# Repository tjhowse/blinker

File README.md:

# Blinker

This is a project to create a long-lifespan solar powered device that blinks
a morse code message. All of the CAD, code and PCB design is open source, and
created with open source tools.

CAD: https://www.freecadweb.org/

PCB: https://www.kicad.org/

Code: Python and C.

Build journal/docs: https://wiki.tjhowse.com/doku.php?id=projects:blinker:overview

## V2

I2C EEPROM

https://www.st.com/en/memories/m24128-bf.html

## Component rev history

Swapped out the schottky diode for a version in JLC's basic parts list.

### Old:

https://jlcpcb.com/partdetail/23350-B5817WSSJ/C22623

20V 450mV@1A 1A SOD-323 Schottky Barrier Diodes (SBD) ROHS

### New:

https://jlcpcb.com/partdetail/GuangdongHottech-1N5819WS/C191023

40V 600mV@1A 1A SOD-323 Schottky Barrier Diodes (SBD) ROHS

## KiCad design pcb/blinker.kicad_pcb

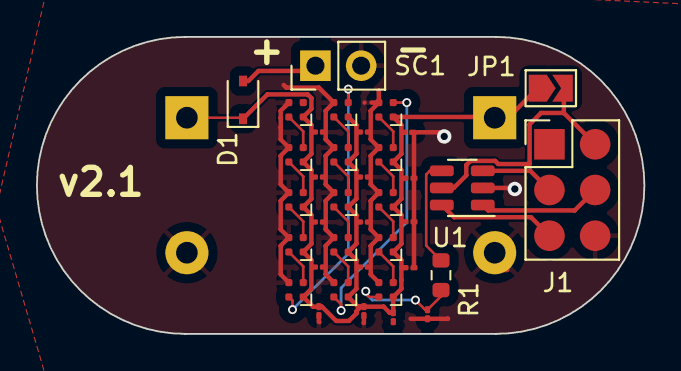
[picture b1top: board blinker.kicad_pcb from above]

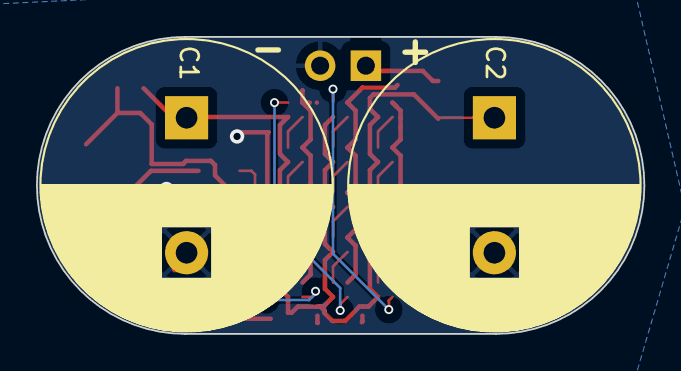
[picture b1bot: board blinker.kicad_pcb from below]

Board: 2 copper layers, 33.8 x 16.5 mm, 39 parts (2 on the bottom side), 23 nets.

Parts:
C1, C2: C_Polarized; CP_Radial_D16.0mm_P7.50mm
C3, C4, C5, C6, C7, C8, C9, C10, C11, C12, C13, C14, C15, C16, C17: 0.1uF; C_01005_0402Metric
C18: 120pF; C_01005_0402Metric
D1: D_Schottky; D_SOD-323
D2, D3, D4, D5, D6, D7, D8, D9, D10, D11, D12, D13, D14, D15, D16: LED; LED_LTST-E133CEGBK
J1: ISP; AVRISP_6PAD
JP1: Jumper_2_Open; SolderJumper-2_P1.3mm_Open_TrianglePad1.0x1.5mm
R1: 33Ω; R_0603_1608Metric
SC1: 3; PinHeader_1x02_P2.54mm_Vertical
U1: ATtiny10-TS; SOT-23-6

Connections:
2.7VCC: C1.1, C2.1, C3.2, C4.2, C5.1, C6.2, C7.2, C8.2, C9.2, C10.2, C11.2, C12.2, C13.2, C14.2, C15.2, C16.2, C17.2, D1.1 (K), D2.1 (VDD), D3.1 (VDD), D4.1 (VDD), D5.1 (VDD), D6.1 (VDD), D7.1 (VDD), D8.1 (VDD), D9.1 (VDD), D10.1 (VDD), D11.1 (VDD), D12.1 (VDD), D13.1 (VDD), D14.1 (VDD), D15.1 (VDD), D16.1 (VDD), JP1.1 (A)
5VCC: J1.2, JP1.2 (B), U1.5 (VCC)
/SLR_IN: D1.2 (A), SC1.1 (+)
GND: C1.2, C2.2, C3.1, C4.1, C5.2, C6.1, C7.1, C8.1, C9.1, C10.1, C11.1, C12.1, C13.1, C14.1, C15.1, C16.1, C17.1, C18.1, D2.3 (VSS), D3.3 (VSS), D4.3 (VSS), D5.3 (VSS), D6.3 (VSS), D7.3 (VSS), D8.3 (VSS), D9.3 (VSS), D10.3 (VSS), D11.3 (VSS), D12.3 (VSS), D13.3 (VSS), D14.3 (VSS), D15.3 (VSS), D16.3 (VSS), J1.6, SC1.2 (-), U1.2 (GND)
LEDSTRING: R1.1, U1.4 (PB2)
unnamed: C18.2, D2.2 (DIN), R1.2
unnamed: D2.4 (DOUT), D3.2 (DIN)
unnamed: D3.4 (DOUT), D4.2 (DIN)
unnamed: D4.4 (DOUT), D5.2 (DIN)
unnamed: D5.4 (DOUT), D6.2 (DIN)
unnamed: D6.4 (DOUT), D7.2 (DIN)
unnamed: D7.4 (DOUT), D8.2 (DIN)
unnamed: D8.4 (DOUT), D9.2 (DIN)
unnamed: D10.4 (DOUT), D11.2 (DIN)
unnamed: D9.4 (DOUT), D10.2 (DIN)
unnamed: D11.4 (DOUT), D12.2 (DIN)
unnamed: D12.4 (DOUT), D13.2 (DIN)
unnamed: D13.4 (DOUT), D14.2 (DIN)
unnamed: D14.4 (DOUT), D15.2 (DIN)
unnamed: D15.4 (DOUT), D16.2 (DIN)
RESET: J1.5, U1.6 (~RESET/PB3)
ROMSCL: J1.3, U1.3 (PB1)
ROMSDA: J1.4, U1.1 (PB0)

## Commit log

2022-01-26 More.
2022-01-26 About to route PCB.
2022-01-26 Ignore kicad backups.
2022-01-26 Remove backups.
2022-01-26 Routed
2022-01-26 routed.
2022-01-26 Update readme, muck about with importing the circuit model to freecad.
2022-01-26 Final PCB design?
2022-01-26 Fix zener selection.
2022-01-26 Gotta fix the rotation on U1.
2022-01-27 v1.0 PCB
2022-01-27 Fix readme.
2022-01-28 Add fab drawing.
2022-02-17 Fix rotation of D2. The JLC team picked this up and fixed it on v1.0.
2022-02-25 Discharge testing logs
2022-02-26 Hack hack.
2022-02-27 Add basic readme.
2022-02-27 Change vector name. Try interrupt-only mode.
2022-02-27 Finally working. Cleanup time.
2022-02-27 Working better.
2022-02-27 Readme update
2022-02-27 Improve byte sequence generator.
2022-02-27 Add some docs.
2022-02-27 Failing to trim some bytes.
2022-02-27 Running power consumption tests.
2022-02-27 Drawing changes
2022-02-27 Remove these weird files.
2022-02-27 Fix line endings
2022-02-27 Add test logs.
2022-02-27 Saved two bytes!
2022-02-27 Worse?
2022-02-28 Revert back to code.1.0. Another foray into size optimisation may be fruitful.
2022-02-28 Experimenting with max message size.
2022-02-28 Don't empty the sequence file if the new string is too long.
2022-02-28 Add a space instead of invalid characters
2022-02-28 Add through-hole pads for external LED. Reduce thermal relief spoke thickness on fill zones to 0.01 in
2022-02-28 Update version number on silkscreen.
2022-02-28 Add very dodgy testing code.
2022-03-01 This is fun, but largely pointless.
2022-03-02 Strip punctuation in the sequence.h comment to match the generated sequence.
2022-03-02 Add numbers and comedy to morse encoding.
2022-03-06 Add datasheet for zener.
2022-03-07 More datasheets.
2022-04-25 Replace cap disconnect jumper with solder bridge.
    Replace 10-pin AVRISP with 6-pad version.
    Rearrangements
2022-04-26 Minor adjustments.
2022-04-26 As ordered
2023-04-09 Improvements
2023-04-09 Add datasheet.
2023-04-16 v1.2 of PCB
2023-05-02 Notes on arduino IDE.
2023-05-10 Tweaks.
2023-05-17 very crude mass blink watching code.
2023-05-17 add config file for watcher.
2023-05-17 Linux-world improvements
2023-05-17 Moving boxes.
2023-05-19 goodish
2023-05-19 Kinda working.
2023-05-28 Add lasercut box scad
2025-07-11 Migrate to kicad 9
2025-07-12 Working.
2025-07-17 Various things, and also stuff.
2025-07-18 Add datasheet for LED, testing character timings.
2025-07-19 Add a helper script.
2025-07-20 Making progress
2025-07-20 Add readability, and save two bytes? somehow?
2025-07-22 Shrink program by pre-processing bitmaps so they don't need shuffling at runtime.
2025-07-22 Improve text preprocessing.
2025-07-24 Adding decoupling caps and RC filter.
2025-07-25 Nearly ready to order.
2025-08-13 Improve box
2025-08-14 Fix 0402 metric vs imperial problem.
2025-09-17 PCB footprint fixes. Still wrong data bus direction.
2025-09-18 Fix character encoding for some characters.
2025-10-03 Reverse LED data bus direction.
2025-10-10 Add other colours.
2025-10-10 Add deep sleeping between letters.
